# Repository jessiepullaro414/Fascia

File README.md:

# Fascia — KiCad schematic + PCB

Companion KiCad project for "Fascia", a 10-inch Android Automotive touch
display head unit: sibling to
[`manifold-pcb`](https://github.com/jessiepullaro414/Manifold),
[`thermo-pcb`](https://github.com/jessiepullaro414/Thermo) and `ecu-pcb`,
same 12V automotive constraints as the rest of the family.

Unlike the rest of the family this is a **two-board** project, because the
panel is physically detached from the main board and sits across the dash
from it:

1. **Carrier board** (behind the dash) — a Toradex Verdin iMX95 System on
   Module on a custom carrier: automotive 12V front end, LVDS display
   output via a DSI-to-LVDS bridge, backlight control, CAN FD to talk to
   `ecu-pcb`, line-level audio pre-outs to an external amplifier, a
   microphone input, and USB-C for wired CarPlay / Android Auto.
2. **Panel board** (in the bezel) — terminates the ribbon at the screen:
   panel LVDS connector, capacitive touch controller, backlight LED
   connector.

Bluetooth and Wi-Fi need no carrier hardware — they come with the
module's `WB` variant.

## Status

**PCB placed and routed to within 3 connections.**
`build_pcb.py` generates `Fascia.kicad_pcb`: 118 footprints, 574 pads
netted across 129 nets, six layers, on a **148 x 71 mm** board.
`route_board.py` (ported from the sibling boards) routes it with
FreeRouting, widens the power trunks, pours GND on In1 and In4, and then
asks `kicad-cli` DRC how many connections are really open. After a
150-pass run **3 connections are still unrouted**: `AOUT_RL_N` (codec to
the audio connector), `U9_ADR1_TIE`, and `LVDS_A_Y0N` (bridge to panel
connector). FreeRouting oscillated between 3 and 4 for the last 100
passes, so more passes of the same run will not close them; they need a
second stochastic attempt or hand-routing. `run_drc.py` reports
**schematic parity 0**, 12 `lib_footprint_mismatch` findings that are a
KiCad tooling artifact, and one silkscreen-over-mask finding.

Nothing about the differential pairs is tuned: FreeRouting does not
length-match, so the DSI and dual-link LVDS pairs are ordinary routed
nets with no impedance control. `route_board.py` prints the resulting
intra-pair skew so it is a number, not a guess.

Placement uses the **same skyline bottom-left packer as `manifold-pcb`
and `thermo-pcb`**, ported rather than reinvented, with three additions
this board needed:

- **Every part is tried both unrotated and rotated 90 degrees**, and goes
  wherever it yields the lowest resulting top edge. That is what turns
  the tall pin-header connectors on their sides and lets the 0603s
  backfill the low spots beside the big parts.
- **Keepouts are real packer inputs**, not checks applied afterwards.
- **The bridge, socket and panel connector are placed first** (`PIN_FIRST`
  in `build_pcb.py`), so the DSI-to-LVDS bridge sits beside the Verdin
  socket instead of 75 mm away. Area order alone had put it there, and
  nearly every open net in the first routing run was at that bridge.
- **A passive goes near its own IC** (`PULL`). Once its anchor IC is
  down, a passive takes the slot closest to it, with a height penalty so
  it cannot strand a void below. Plain lowest-gap order had put a
  pull-up 130 mm from the chip it belongs to. Estimated wirelength fell
  from 7,612 to 5,895 mm (`tools/placement_metric.py`), and FreeRouting
  at 12 passes went from 22 unrouted to 4.
- Spacing between parts (`CLEAR`) is 2.0 mm, up from 1.3. That alone took
  12-pass routing from 22 unrouted to 11, at a cost of 7 mm of height.

Group membership is derived from the netlist: each part joins whichever
IC or connector it shares the most **non-rail** nets with. Rails are
excluded deliberately: GND touches everything and would make every part
look equally related to everything else.

The Verdin socket is rotated 90 degrees as part of that. Its footprint is
36 x 79 mm, tall and narrow; on its side it is 79 x 36 mm and the board
becomes landscape, which is also the shape a dash opening wants.

**Schematic complete — every block wired except the backlight.**
`build_schematic.py` generates a real, KiCad-loadable schematic
containing the Verdin iMX95 X1 connector, the 12 V automotive front end,
the 5 V buck, the 1.8 V and 3.3 V rails, CAN FD, the SN65DSI85-Q1
DSI-to-LVDS bridge, the PCM3168A-Q1 audio subsystem with its level
shifters, the USB-C port, and the control/sequencing block. No PCB yet.

`kicad-cli sch erc` reports **10 violations**, and every one is either
blocked on a datasheet that has not arrived or deliberately optional:

| What | Count | Why it is still open |
| --- | --- | --- |
| `PWM_3_DSI`, `GPIO_10_DSI` | 2 | Backlight — needs the iFan string voltage and current |
| `USB_2_*` | 4 | Panel touch link — needs the panel's touch interface confirmed |
| `CAN_2_*` | 2 | Optional second CAN bus; no consumer chosen |
| `DSI_IRQ` | 1 | Bridge interrupt; wants a spare 1.8 V module GPIO |
| `IGN_SENSE` | 1 | Ignition sense; wants a module ADC input |

**160 pins carry real NoConnect items and 40 signal nets are wired.**

**Footprints are assigned and verified.** Every part maps to a real
footprint, and the build checks that each named file actually exists — a
mistyped library path is otherwise invisible until the netlist reaches
the PCB editor and silently drops the part.

### The LM61460-Q1 footprint is generated, not borrowed

TI's RJR0014A (VQFN-HR-14) has no KiCad library footprint, and it is not
something a generic QFN generator can produce: the pads are all different
sizes, unevenly spaced, and **the four corner pads are L-shaped**.

`tools/build_lm61460_footprint.py` builds it. The geometry is not
eyeballed off the drawing — the LAND PATTERN EXAMPLE on page 55 of TI
SNVSB70F is real vector art, so the pad rectangles were extracted from
the PDF's own path data and only the *scale* had to be inferred, from a
dimension the drawing states outright (pad 10 is 2.4 × 0.4 mm). That
scale then reproduced pad 10's 0.400 mm height exactly, which is what
makes the rest of the extraction trustworthy.

Each L-shaped pad is built from **two rectangles sharing one pad
number** — a real KiCad construction this project has met before, in a
Keystone fuse holder with two physical pads both numbered "1". It is far
safer than approximating an L with its bounding box, which would put
copper in the notch and eat the clearance to the neighbouring pads.

All four notches face the *outer* corner of the pattern, confirmed by
rendering the drawing around pads 1, 9 and 11 rather than assuming the
symmetry held.

The generator verifies itself twice: internally, that the pad table is
coherent (pin numbering, which pads are L-shaped, pad 10's dimensions,
overall extent, and that no two *different* pins overlap), and then by
**loading the result back through KiCad's own engine**. That second check
earned its place immediately — the first version emitted trailing
`; PINNAME` comments on the pad lines, and KiCad's s-expression format
has no comment syntax, so the whole library failed to load with nothing
more useful than "Unable to load library".

The Verdin module plugs into a standard DDR4 SODIMM socket, and KiCad's
`SODIMM-260_DDR4_H4.0-5.2_OrientationStd_Socket` has exactly 260 pads
numbered 1–260 — a direct match for the extracted pinout, so the biggest
footprint risk on this board turned out to be no risk at all.

### Exposed pads are three different decisions

Every one of these footprints numbers its exposed pad N+1 — 65 on the
TQFP-64s, 25 on the VQFN-24, 9 on the SON-8s. Each symbol therefore
carries an explicit `EP` pin, so what happens to that pad is a visible
decision on the schematic rather than an accident of the pad having no
net:

| Part | Exposed pad |
| --- | --- |
| **LM74930-Q1** | **NoConnect — must float.** The datasheet forbids grounding it |
| TLV767-Q1, TPS2557-Q1 | GND |
| SN65DSI85-Q1, PCM3168A-Q1 | GND (PowerPAD is reference ground) |

The LM74930-Q1's NoConnect is load-bearing: without an explicit pin,
that pad is merely netless, and nothing on the drawing would stop a
later ground-stitching pass from claiming it.

What is already final:

- all 260 X1 pins exist, banked into 6 units
- 47 GND pins tied to ground, 5 VCC pins tied to +5V
- 158 unused pins carrying real `NoConnect` items
- **LM74930-Q1 front end fully wired** — back-to-back FETs with `A` and
  `OUT` on the shared source node, sense resistor with its 50 Ω tap into
  `CS+`, `OVCLAMP` tied to `OV` for clamp-with-breaker rather than plain
  disconnect, and the OV/UVLO dividers, timer, ILIM and IMON networks
- **LM61460-Q1 5 V buck fully wired** — `BIAS` to the output rail (valid
  because Vout ≤ 12 V), boot network through `RBOOT`, FB and EN dividers,
  `RT`, and pull-ups on the open-drain `FLT` and `PGOOD` outputs
- **TLV767-Q1 1.8 V LDO wired** — an LDO rather than a buck on purpose:
  small load, and no switching noise added to a board carrying LVDS next
  to a car radio. This rail exists because the module's I/O is 1.8 V
  logic; it feeds the CAN transceiver's VIO now and the bridge later
- **TCAN1044V-Q1 CAN FD link wired** — split termination (2×60 Ω with a
  midpoint capacitor to ground, which shunts common-mode noise on a bus
  leaving the enclosure on a harness), separate 5 V VCC and 1.8 V VIO
  decoupling, and a pull-down on `STB` because the part's internal
  pull-up would otherwise wake it in standby
- the module's `CAN_1_TX` / `CAN_1_RX` now reach the transceiver
- **SN65DSI85-Q1 bridge wired** — DSI channel A in, both LVDS links out,
  all twelve VCC pins on 1.8 V, `VCORE` treated as the 1.1 V *output* it
  is with its 1 µF, `REFCLK` resistor-pulled to ground since the pixel
  clock comes from the D-PHY clock, `ADDR` strapped low, and the unused
  DSI channel B inputs plus both RSVD pins left genuinely unconnected
  with NoConnect items rather than tied off
- `J4` panel LVDS connector, **provisional** — carries all 20 LVDS
  signals, but its real pin order and pin count await the panel datasheet
- **PCM3168A-Q1 audio codec wired** — five differential pre-outs (front
  L/R, rear L/R, sub) to `J5`, microphone into the first differential ADC
  input, TDM on `DIN1`, `MODE` strapped low for the I2C control port
- **A 3.3 V rail and two SN74AXC4T245-Q1 level shifters**, because the
  codec's digital domain cannot be wired directly to the module — see
  "The audio block needs level shifters" below
- **I2C crosses domains through the classic two-FET translator** rather
  than a push-pull part, which cannot pass an open-drain bus
- **USB-C port wired** — TPS2557-Q1 switching VBUS with a ~3.3 A limit,
  Rp resistors on both CC pins advertising 3 A from a downstream-facing
  port, ID strapped low for host mode, a divided VBUS sense back to the
  module, and ESD on every pin a passenger can touch. No PD controller
  and no negotiation firmware.
- **Control and sequencing wired** — JTAG header, power/recovery/reset
  buttons, and the RTC coin cell behind the ≥47 kΩ current-limiting
  resistor the datasheet requires (a lower value can stop the module
  booting). `CTRL_PWR_EN_MOCI` now gates the 1.8 V and 3.3 V LDOs, so
  the carrier rails follow the module instead of racing it at power-on.
- every pin on all nine ICs either netted or explicitly NoConnected

### The generator checks for silently merged nets

Blocks are laid out independently, so two can drift into the same region
and land one net's stub endpoint exactly on another's. That **merges the
two nets** — electrically catastrophic and near-invisible on the drawing.
It happened twice while building this schematic:

1. a codec decoupling cap's ground stub landed on the power tree's
   `UVLO_DIV` label;
2. the USB block's `USB_ILIM` stub landed on connector unit D's
   `USB1_VBUS_SENSE` stub.

ERC does report this as `multiple_net_names`, but only for the pair it
happens to notice and only after the fact. `build_schematic.py` now
records every terminated coordinate — pin positions *and* stub
endpoints, for both generic parts and the X1 connector — and fails
loudly, naming both nets and both owning references. The first version
of that check scanned only label positions and missed the second case
entirely, which is why it now tracks points rather than labels.

### The audio block needs level shifters (and why that is not optional)

The PCM3168A-Q1 has two supply domains: analog VCC at 4.5–5.5 V and
**digital VDD at 3.0–3.6 V**. VDD cannot be run at 1.8 V, so the codec
cannot share the module's logic level. Reading the electrical table
makes the consequence sharper than "it needs a translator":

| | Codec | Verdin |
| --- | --- | --- |
| Input high, min | **2.0 V** | drives 1.8 V max |
| Output high, min | **2.4 V** | **2.1 V absolute maximum** |

The first row means the module cannot reliably drive the codec. The
second row is the dangerous one: the codec's output high is *above the
module's absolute maximum rating*. Wired directly, the codec-to-module
direction would not merely fail — it would damage the module.

So every digital line between them is translated: I2S and the clocks
through SN74AXC4T245-Q1 translators, and I2C through the classic
two-N-FET open-drain circuit, because a push-pull translator cannot pass
a bus where either end may pull low.

What exists right now:

- `tools/extract_verdin_pinout.py` — extracts the full 260-pin Verdin
  iMX95 X1 connector pinout from Toradex's own hardware datasheet.
- `verdin_pinout.py` — the generated result: all 260 pins, 47 GND, 5 VCC,
  and the 20 LVDS pins, cross-checked against a second independent table
  in the same document.
- `verdin_x1.py` — functional banking of those 260 pins into multi-unit
  symbol units, with a verifier that proves the banking is a true
  partition of the connector.
- `build_schematic.py` — generates `Fascia.kicad_sch`, `Fascia.kicad_sym`,
  `sym-lib-table` and (on first run only) `Fascia.kicad_pro`.

Three things that were needed to get the first ERC pass down from 268
findings to the real ones, recorded because each cost a debug cycle:

1. **Power symbols must touch the net graphically.** A power symbol's own
   pin sits at its local origin with zero length, so placing it *near* a
   connector pin leaves both dangling — 155 `pin_not_connected` findings.
   The fix is a short stub wire from the pin out to the symbol, which
   also keeps the symbol graphic off the pin name.
2. **PWR_FLAGs need the same graphical reachability.** A flag placed in
   isolation, relying on name-based net merging, does not satisfy
   `power_pin_not_driven` (54 findings). Placing each flag on a real
   point of its net clears it.
3. **`kicad-cli` needs a `.kicad_pro` to resolve `${KIPRJMOD}`.** Without
   one it cannot find the project-local `sym-lib-table` and reports one
   `lib_symbol_issues` warning per placed symbol (60 findings), even
   though the symbols are embedded in the schematic and perfectly valid.

Everything below the "Design decisions" section is a plan, not a
description of something that exists. See "Known open items".

### Why X1 is banked into units

A 260-pin connector cannot be one schematic symbol — at 2.54 mm pitch a
single block is ~330 mm tall, taller than any sheet this project uses.
KiCad's answer is a multi-unit symbol, so `verdin_x1.py` assigns each pin
to a unit based on how *this board* uses the connector:

| Unit | Pins | Contents |
| --- | --- | --- |
| A | 55 | Power and ground |
| B | 16 | Control, sequencing, JTAG, tamper |
| C | 15 | Display — the DSI link to the bridge, plus backlight control |
| D | 16 | Communications — CAN to `ecu-pcb`, I2C, USB 2.0 for touch |
| E | 158 | Unused on this board (gets NoConnect items) |

Banks are derived from pin *names* rather than hand-listed pin numbers,
so re-running the extractor against a newer datasheet revision cannot
silently desynchronise the two files. That only works if the rules stay
exhaustive, which `verify()` enforces: every pin exactly once, nothing
invented, nothing dropped, plus explicit assertions on the two groupings
most worth getting right —

- the **display bank** must be exactly the 15 pins from datasheet
  Table 22, asserted by number rather than trusted to a pattern;
- the **USB split** must put the USB 2.0 data pair in the comms bank and
  SuperSpeed in the unused bank. This board's only USB is a 2.0 host port
  for the panel's touch controller, so the SS pairs are unused *on
  purpose*. Worth an explicit rule because they appear under two
  different naming styles — Verdin-standard `USB_2_SS*` and
  module-specific `USB1_TX1_*`/`USB1_RX1_*` — and a single `USB_` pattern
  silently catches one and misses the other.

Bank E is not filler. Per this project's KiCad notes a deliberately
unused pin needs a real `NoConnect` item, not a stub label, or ERC
reports it as a dangling/isolated label — so the unused pins have to be
enumerated as carefully as the used ones.

## Why this SoC, and why not the one I started with

The project began as "10-inch Android Automotive display on an NXP
i.MX 93". **The i.MX 93 cannot run Android**, and this was worth catching
before any board work started:

- The i.MX 93 has no 3D GPU — only the PXP 2D pixel pipeline.
- Since Android 10, NXP has excluded GPU-less i.MX parts from Android
  support outright, because Android's GPU and extension requirements
  can't be met. Running it would mean maintaining a private Android fork
  on software rendering.
- NXP's current i.MX Android BSP covers the 8M Mini/Nano/Plus/Quad, 8ULP,
  8QuadMax/XPlus and i.MX 95. Not the 93.

Replaced with the **i.MX 95**, which has an Arm Mali-G310 (OpenGL ES 3.2,
Vulkan 1.2, 2D+3D), is on NXP's Android BSP list, and is automotive
qualified.

### Why a SoM instead of a raw i.MX 95

A raw i.MX 95 is a 19×19 mm BGA paired with LPDDR5. That forces HDI
construction (laser microvias, blind/buried vias, 12–14 layers just to
escape the BGA) and roughly 90 length- and skew-matched LPDDR5 nets.

That last part is the disqualifier for this project specifically:
FreeRouting cannot do length-matched differential DDR routing, so the DDR
work would have to be manual — which directly contradicts this family's
rule that the generator scripts are the source of truth and the board is
always regenerated, never hand-edited.

Putting the SoC on a **Toradex Verdin iMX95** module moves the LPDDR5 and
its HDI stackup onto a part Toradex has already qualified, and leaves a
carrier board that is connectors, power and differential pairs — squarely
inside what the existing generate → route → verify pipeline handles.

## Design decisions

### Display link: 1920×1200, DSI-to-LVDS bridge on the carrier

The panel is detached and 20 cm–1 m away across the dash, so the link
that crosses that gap must be **LVDS** — differential and low-swing, so
it survives alternator and ignition noise. Options for the long run:

| Option | Verdict |
| --- | --- |
| **LVDS over shielded FFC** | **Chosen for the cable run.** Robust over a dash-length ribbon, and what 10.1" panels natively accept. |
| MIPI DSI direct to the panel | Rejected. D-PHY is designed for on-PCB or very short flex (~15–20 cm); unshielded ribbon across a dash is an EMI problem. |
| HDMI | Not native on the module. Needs a DSI-to-HDMI bridge on the carrier *and* a receiver board behind the panel bridging back. Two extra bridges. |
| FPD-Link III / GMSL2 | The right answer for genuinely long runs (10 m+), overkill and expensive here. |

**How the LVDS gets generated is the part that took real work.**

The module's own display ceilings, from datasheet Table 3: **LVDS 1× up
to 1920×1080**, **MIPI DSI 1× quad lane up to 4K**.

The 10.1" panel market is overwhelmingly **16:10** (1280×800 and
1920×1200), not 16:9. 1920×1200 needs ~154 MHz of pixel clock, which is
**above the module's 1920×1080 native LVDS ceiling** — both Toradex and
NXP's summary cap i.MX 95 LVDS at 1080p60. Forum figures of 170 MHz for
dual-channel split mode are **i.MX 6**, a different generation, and must
not be extrapolated to this part.

So: take **MIPI DSI off the module** (where 1920×1200 is far inside the
4K ceiling) and convert to dual-channel LVDS **on the carrier board**,
right at the ribbon connector, with a **TI SN65DSI85-Q1** — AEC-Q100
qualified, dual-channel LVDS out, 24 bpp, pixel clock 25–154 MHz.

The DSI run stays on-PCB where D-PHY is happy (centimetres); the long,
noisy dash run is still LVDS. Cost is one bridge IC.

**The module's native LVDS pins (88–144) are therefore unused.** They
remain documented in `verdin_pinout.py` in case the design ever falls
back to 1080p native.

**Unexpected benefit:** the whole DSI pin group sits on Verdin-standard
*Reserved* pins (17–55) rather than the *Module-specific* pins native
LVDS uses. This design is therefore **more** portable to other Verdin
modules than the native-LVDS version would have been — it inverts the
portability caveat noted below.

**Confirmed DSI pin group** (Verdin iMX95 datasheet Table 22), which
carries not just the lanes but every control signal the bridge and
backlight need:

| X1 pin | Signal | Role |
| --- | --- | --- |
| 23 / 25 | DSI_1_D3_N / _P | DSI data lane 3 |
| 29 / 31 | DSI_1_D2_N / _P | DSI data lane 2 |
| 35 / 37 | DSI_1_CLK_N / _P | DSI clock |
| 41 / 43 | DSI_1_D1_N / _P | DSI data lane 1 |
| 47 / 49 | DSI_1_D0_N / _P | DSI data lane 0 |
| 53 / 55 | I2C_2_DSI_SDA / SCL | SN65DSI85-Q1 configuration |
| 17 | GPIO_9_DSI | bridge enable |
| 19 | PWM_3_DSI | backlight brightness |
| 21 | GPIO_10_DSI | backlight enable |

### SN65DSI85-Q1: confirmed from the TI datasheet (SLLSEJ4B)

The mode this whole design depends on is **explicitly supported** —
datasheet Table 5, "Single DSI Input to Dual-Link LVDS":

> Single DSI Input on Channel A to Dual-Link LVDS output with Odd pixels
> on Channel A and Even pixels on Channel B.

Register configuration for that mode:

| CSR | Field | Value |
| --- | --- | --- |
| 0x10.6:5 | `DSI_CHANNEL_MODE` | `01` — single-channel DSI receiver |
| 0x10.4:3 | `CHA_DSI_LANES` | `00` — four lanes enabled |
| 0x18.4 | `LVDS_LINK_CFG` | `0` — dual-link LVDS |
| 0x18.3 | `CHA_24BPP_MODE` | `1` — 24 bpp |
| 0x18.1 / 0x18.0 | `CHA/CHB_24BPP_FORMAT1` | selects Format 1 vs Format 2 |

Other confirmed facts that drive the schematic:

- **AEC-Q100 Grade 2, −40 °C to +105 °C ambient.** Better rated than the
  Verdin module itself, and consistent with the rest of this family.
- **Single 1.8 V supply** (VCC 1.65 / 1.8 / 1.95 V). No second rail.
- **HTQFP-64 (PAP)** with thermal pad. RθJA 36.1 °C/W, max case
  temperature 92.2 °C — the pad needs a real thermal via field.
- **REFCLK (pin 17) is optional** — the LVDS pixel clock can be sourced
  from the free-running D-PHY clock instead. If unused it **must be
  pulled to ground through an external resistor**, not left floating.
- **ADDR (pin 64)** selects the I2C target address; if strapped high it
  must go to the *same* 1.8 V rail as VCC, not any other 1.8 V source.
- **IRQ (pin 33)** is an interrupt output back to the SoC.
- **EN** may be driven by `GPIO_9_DSI` or by an RC (≈200 kΩ + ≈200 nF).
  It must only go high *after* VCC is valid. To reset with VCC already
  high, EN must be held low ≥10 ms.
- **Sequencing constraint for the driver:** the DSI CLK lane must be in
  HS and the DSI data lanes driven to LP11 while the device is in reset,
  before EN is asserted.
- For 18 bpp the `Y3` pairs are left NC; at 24 bpp all four data pairs
  per link are used — so the panel connector carries 10 pairs.
- `CHA_SYNC_DELAY` must be programmed to at least 32 pixel clocks.

**Everything is configured over I2C — there is no format strapping.**
That is a meaningful de-risking result: the VESA-versus-JEIDA mapping
question is a *software* choice (`24BPP_FORMAT1`), so picking the panel
later cannot force a board respin over it.

### Timing margins — corrected

An earlier revision of this file claimed 1920×1200 sat "exactly at the
bridge's 154 MHz ceiling". **That was wrong**, and the error mattered:
the 25–154 MHz figure is the **LVDS output clock per link**, and in
dual-link mode each link carries half the pixels. TI's own power-table
reference case is literally 1920×1200 dual-link with
**LVDS CLK OUT = 81.6 MHz**.

The real picture, with every number now confirmed against a primary
source:

| Constraint | Value | Limit | Utilisation |
| --- | --- | --- | --- |
| i.MX 95 DSI transmit, per lane | ~925 Mbps | **2500 Mbps** | **~37% — huge headroom** |
| LVDS output clock, per link | ~81.6 MHz | 154 MHz | ~53% — comfortable |
| **Bridge DSI input, per lane** | ~925 Mbps | **1 Gbps** | **~93% — the bottleneck** |

The i.MX 95 side is confirmed a non-issue: **IMX95AEC Rev 8, Table 58,
`RATE[TX]` Transmit Serial Data Rate = 80 to 2500 Mbps per lane**, and
the feature summary lists "1x 350 MHz MIPI-DSI (4-lane, 2.5 Gbps/lane)
supporting 4kp30 or 3840 x 1440p60".

So the **SN65DSI85-Q1 is the sole bottleneck** in the chain. That is
acceptable — TI documents 1920×1200 as a supported use case for this
part — but it means the bridge, not the SoC, is what to re-examine if
the timing ever fails to close.

The same datasheet confirms the native LVDS ceiling recorded above:
"2x 1080p60 LVDS Tx (2x 4-lane or 1x 8-lane)".

- 1920×1200p60 CVT-RB ≈ 154 MHz pixel clock × 24 bpp = ~3.70 Gbps across
  4 lanes = ~925 Mbps/lane. Under the bridge's 1 Gbps limit, with ~7%
  headroom.
- With **standard** (non-reduced) blanking the pixel clock is ~193 MHz →
  ~1.16 Gbps/lane, which **exceeds** the bridge limit (though not the
  SoC's). Reduced-blanking timing is therefore mandatory, not merely
  preferable.
- Fallback remains 1920×1080, which relaxes the DSI side to
  ~830 Mbps/lane.

### Layout constraints (i.MX 95 Hardware Design Guide UG10210 Rev 2.0)

- **100 Ω differential** for MIPI DSI *and* LVDS, ±10% (Table 40). Also
  50 Ω single-ended for everything else unless specified. This sits
  comfortably inside the SN65DSI85-Q1's own 90–132 Ω LVDS output range.
- For MIPI-DSI compliance tests 1.1.4/1.1.5, keep **parasitic
  capacitance of each DSI trace below 10 pF** — relevant because the DSI
  run crosses the carrier from X1 to the bridge.
- The module's unused native LVDS pins are simply left **not connected**
  (datasheet Table 4). The `VDD_LVDS_1P8`-to-ground-via-10 kΩ guidance in
  that same table applies to the SoC, which is Toradex's side of the
  boundary, not this carrier's.

Note the Verdin carrier must still follow Toradex's own Carrier Board
Design Guide (doc 108140) for anything X1-side; UG10210 describes the
raw SoC.

For reference, the module's native LVDS pins, should the fallback be
needed:

| X1 pin | Channel 0 | X1 pin | Channel 1 |
| --- | --- | --- | --- |
| 88 / 90 | LVDS0_CLK_N / _P | 118 / 120 | LVDS1_CLK_N / _P |
| 94 / 96 | LVDS0_D0_N / _P | 124 / 126 | LVDS1_D0_N / _P |
| 100 / 102 | LVDS0_D1_N / _P | 130 / 132 | LVDS1_D1_N / _P |
| 106 / 108 | LVDS0_D2_N / _P | 136 / 138 | LVDS1_D2_N / _P |
| 112 / 114 | LVDS0_D3_N / _P | 142 / 144 | LVDS1_D3_N / _P |

### Candidate panels evaluated

Real parts found, with the specs that actually drive the board design:

**Selected: iFan IF101GRL192-120B** (2026-08-16), pending the vendor
datasheet and pricing. Chosen mainly on temperature — it is a full 10 °C
better at both ends than the other 1920×1200 candidate, which is the
difference between reliable and marginal on a sun-baked dash — with 89%
DCI-P3 gamut as a real bonus for image quality.

<https://ifan-display.com/product/10-1-inch-touch-panel-1000-nits-wide-color-gamut-1920x1200/>

| Part | Res | Nits | Interface | Touch | Bonded | Temp |
| --- | --- | --- | --- | --- | --- | --- |
| **iFan IF101GRL192-120B** ← selected | 1920×1200 | 1000 | LVDS, 60-pin | **PCAP inc.** | ? | **−30 to +80 °C** |
| Riverdi RVT101HVLNWC00-B | 1280×800 | ~1000 | LVDS | PCAP inc. | **yes** | industrial |
| CDTech S101BWU78EP | 1920×1200 | 1000 | LVDS, 45-pin FPC | no | no | −20 to +70 °C |
| CDTech S101HWX101ED | 1280×800 | 1000 | 4-lane LVDS, 40-pin FPC | no | no | −30 to +80 °C |
| CDTech S101HWX80NP-FC81 | 1280×800 | 350 | 1-ch LVDS, 30-pin | ILI2511 (USB) | no (G+G) | −20 to +70 °C |
| AUO G101UAN02.0 | 1920×1200 | 800 | **MIPI** | no | no | **−10 to +60 °C** |

**The market bifurcates, and neither half is the full target spec:**

- You can get **1920×1200 + 1000 nit + touch** (iFan), but optical
  bonding is unconfirmed and there is no public datasheet — it is a
  contact-the-vendor part.
- Or you can get **productized optical bonding + PCAP + real datasheets
  + distributor stock** (Riverdi), but only at 1280×800.

The full combination is realistically a **semi-custom order with MOQ**,
not an off-the-shelf purchase.

AUO's G101UAN02.0 is ruled out on two counts despite being the obvious
1920×1200 name: it is **MIPI, not LVDS** (which would put D-PHY on the
dash ribbon, the thing this whole design avoids), and −10 to +60 °C is
unusable in a car.

Three things to carry forward:

1. **The backlight boost designs are not interchangeable** — 27–34 V at
   240 mA versus 13.5–17 V at 360 mA versus 5 V at 530 mA are three
   different converters. The panel must be chosen before the backlight
   circuit is designed. iFan publishes only a total figure (9.32 W), so
   the string configuration has to be asked for.
2. **Temperature does not track resolution.** CDTech's 1920×1200 part is
   −20 to +70 °C while their 1280×800 is −30 to +80 °C. A dash bakes in
   sun, so this is a real selection criterion, not a footnote — it is the
   main reason the iFan part leads.
3. **Touch is often USB, not I2C.** Both CDTech modules with touch use
   USB controllers (ILI2511), and iFan lists "USB/I2C". This matters —
   see below.

### Touch interface: USB may beat I2C over this cable run

The original plan assumed I2C touch. The market says otherwise, and on
reflection USB is probably the better engineering choice here anyway:

- **I2C is single-ended** and was designed for on-board use. Over 20 cm
  it is fine; over a metre it is marginal — bus capacitance eats the
  rise time and there is no noise rejection in a car's environment.
- **USB is differential and designed for cables.** A metre is nothing.
  It also arrives as a standard HID device, so Android needs no custom
  touch driver or device-tree work.
- Cost is one differential pair on the ribbon instead of two
  single-ended wires, and a USB host port on the carrier — which the
  Verdin already has.

Decision still open, but it should be made on cable length, not on
which is simpler on paper.

### Power tree and part selection

Every part below was verified against its own datasheet, not chosen from
memory. Two of them corrected an earlier wrong guess, noted inline.

| Role | Part | Key evidence |
| --- | --- | --- |
| Front-end protection | **LM74930-Q1** | AEC-Q100 grade 1 (−40/+125 °C), 4–65 V in, reverse protection to −65 V, adjustable OC/OV, circuit breaker, "meets automotive ISO7637 transient requirements with a suitable TVS diode" |
| 12 V → 5 V buck | **LM61460-Q1** | AEC-Q100 grade 1, 3–36 V in (42 V transient), 6 A, synchronous, low-EMI with spread spectrum |
| CAN FD | **TCAN1044V-Q1** | AEC-Q100 grade 1, VIO 1.7–5.5 V with explicit 1.8 V support, CAN FD to 8 Mbps, ±58 V bus fault protection |
| DSI→LVDS bridge | **SN65DSI85-Q1** | AEC-Q100 grade 2 (−40/+105 °C), single 1.8 V rail, HTQFP-64 |
| Audio codec | **PCM3168A-Q1** | AEC-Q100, 24-bit 6-in/8-out codec, differential outputs, I2S/TDM, 104 dB, 64-HTQFP |
| USB VBUS switch | **TPS2557-Q1** | Automotive, current limit adjustable 500 mA–5 A, FAULT output, dual thermal sensing |
| Wi-Fi / Bluetooth | **on-module** (u-blox MAYA-W260-00B) | Wi-Fi 6, Bluetooth Classic/LE 5.4, two U.FL connectors — comes with the Verdin `WB` variants |

**The module sets two hard constraints** that drove these choices:

- **VCC is 3.135–5.5 V**, so the main rail is 5.0 V.
- **Verdin I/O is 1.8 V logic** (absolute max 2.1 V). This is the
  constraint that eliminates most automotive CAN transceivers.

#### Front-end topology (resolved from the datasheet, not inferred)

TI's own front-page reference circuit for the LM74930-Q1 is titled
**"VBAT 12-V or 24-V With 200-V Unsuppressed Load Dump — Output Clamp"**.
That is this application almost exactly: an unsuppressed alternator on a
1972 car, with the output clamped rather than disconnected.

The back-to-back FET arrangement is easy to get backwards, so it is
written down here:

```
VBAT ──[RSENSE]──┬── Q2 drain            Q2 = pass / load switch  (HGATE)
                 │                       Q1 = ideal diode         (DGATE)
                 Q2 source ──┬── COMMON ──┬── Q1 source
                             │            │
                        OUT (15)      A (2)      ← both pins on COMMON
                                                    (common-source pair)
                                       Q1 drain ── VOUT_PROT ── C (24)
```

The resolution: **`A` (2) and `OUT` (15) are the same node.** "Back-to-back
N-channel MOSFETs in common source configuration" means both FET sources
tie together, and the datasheet independently says `A` is "the source of
the external ideal diode MOSFET" while `OUT` is "the common source rail".
`C` (24) is the ideal diode's drain and therefore the protected output.
Direction is confirmed by the ideal-diode spec regulating "10.5 mV **A to
C** forward voltage drop", and by `HGATE` driving "the **first** MOSFET in
the power path".

Reference-design support components, all named in that circuit: `RSENSE`
with `RSET` (50 Ω into `CS+`), `RISCP` on `ISCP`, `RILIM` on `ILIM`,
`RMON` on `IMON`, `CT` on `TMR`, `CVS` on `VS`, `CCAP` across `CAP`–`VS`,
and the `R1`/`R2`/`R3` dividers feeding `OV`/`OVCLAMP` and `UVLO`.

#### The 5 V rail needs splitting

Rough budget, with the module figure still a placeholder:

| Load | Estimate |
| --- | --- |
| Verdin iMX95 | ~3 A @ 5 V (unknown — see open items) |
| USB-C charging | 3 A @ 5 V |
| Bridge, codec, CAN, misc | ~0.5 A |
| **Total on 5 V** | **~6.5 A** |

That is over the LM61460-Q1's 6 A, so **two supplies** rather than one
bigger one: a main rail for the module and peripherals, and a second
dedicated to USB VBUS. Splitting is the better design anyway — a phone
drawing a fault current should not be able to brown out the SoC and
reboot Android. Using the same part twice also keeps the BOM narrow.

The backlight boost is deliberately *not* on the 5 V rail — it runs from
the protected 12 V directly, since the panel wants ~27–34 V and routing
that through 5 V would waste a conversion and eat the budget.

#### Bluetooth comes free with the module

The Verdin `WB` variants carry a u-blox **MAYA-W260-00B**: Wi-Fi 6,
**Bluetooth Classic / LE 5.4**, IEEE 802.15.4, and **two U.FL antenna
connectors already on the SoM**. That means no RF design, no antenna
matching and no radio certification work on this carrier — just two U.FL
cables out to external antennas.

Bluetooth Classic covers A2DP for streaming and HFP for hands-free calls.
Wi-Fi plus Bluetooth together is also exactly what **wireless CarPlay and
Android Auto** need, so the USB-C port is for wired mode and charging
rather than being the only way in.

Cost to record: the datasheet carries separate pin tables for "modules
without Wi-Fi", so the `WB` variant consumes some UART and ADC pins that
would otherwise reach the carrier. The variant has to be locked before
the connector banks are final.

#### Two corrections worth recording

**The CAN transceiver must be the `V` variant.** An earlier draft of this
plan named the TCAN1043-Q1, which only level-shifts to 3.3 V or 5 V — it
cannot talk to 1.8 V logic at all. Worse, within the correct family the
datasheet's own device comparison table reads:

| Part | Low-voltage I/O support on pin 5 |
| --- | --- |
| TCAN1044-Q1 | No — pin 5 is a No-Connect |
| **TCAN1044V-Q1** | Yes — pin 5 is VIO, 1.8–5.5 V |

The suffix is the entire difference. Order the wrong one and the board
assembles perfectly and the CAN link never works.

**The surge stopper is TI's, not the obvious ADI part.** The LTC4364 is
the better-known automotive surge stopper and does something the
LM74930-Q1 does not — it *regulates through* an overvoltage event rather
than disconnecting. But its datasheet order table lists only C, I and H
temperature grades with **no AEC-Q100 qualification**, which fails this
family's standard (see `ecu-pcb`, where the last unqualified part was
deliberately swapped out). The LM74930-Q1 is explicitly `-Q1`.

**Correction — the LM74930-Q1 does clamp through.** An earlier revision
of this file claimed it protects only by disconnecting the load, and
warned that a load dump would therefore collapse the 5 V rail and force
an Android reboot. That was wrong, and reading the pin table and spec
table settled it:

- pin 16 is **`OVCLAMP`**: "connect this pin to OV pin for overvoltage
  clamp with circuit breaker (timer) functionality";
- `OVCLAMP` has its own rising/falling thresholds (0.59 V / 0.45 V),
  separate from the plain `OV` disconnect thresholds;
- the timer spec includes **`I(TMR_SRC_OVCLAMP)`, "TMR source current
  during overvoltage clamp"** — a dedicated clamp state, not a
  disconnect;
- and `N(A_R_Count)` gives **32 auto-retry cycles**.

So it regulates the pass FET through an overvoltage event for a period
set by the TMR capacitor, then opens the breaker if the event outlasts
it, then auto-retries. That is genuine surge-stopper behaviour, and it
removes the reboot risk previously recorded here.

What remains real is that the clamp is **timed, not indefinite**: the TMR
capacitor has to be sized to ride out a 200 ms load dump, and the pass
FET has to survive dissipating it for that long. FET SOA selection is
therefore a genuine design task — see "Known open items".

For scale, the LTC4364 datasheet gives the industry-standard transient
shapes: a general automotive transient of tr = 10 µs / VPK = 80 V /
τ = 1 ms, and **load dump of tr = 5 ms / VPK = 60 V / τ = 200 ms**. The
200 ms one carries the energy that matters.

### Panel quality matters more than resolution here

Recorded because it should drive the panel budget. In a car, in rough
order of impact on how good the display actually looks:

1. **Brightness** — consumer panels (250–400 nits) wash out in direct
   sun; automotive panels run 800–1500 nits. This is the dominant factor
   and it drives the backlight boost design (string current, thermals).
2. **Optical bonding** (OCA/LOCA) — removes the air gap between LCD and
   cover glass that otherwise destroys daylight contrast; also prevents
   condensation.
3. **24-bit colour, not 18-bit** — 6-bit-per-channel LVDS panels band
   visibly on the dark gradients Android Automotive uses.
4. **IPS** — driver and passenger both view well off-axis.
5. **Anti-glare / AR coating.**

Resolution ranks below all of these. The target spec is a 1080p,
~1000-nit, optically-bonded, 24-bit IPS panel.

**Caveat worth recording:** LVDS on Verdin is a *Module-specific*
function, not an Always-Compatible or Reserved one (datasheet Table 6
classifies it `Total 1 / Always Compatible 0 / Reserved 0 /
Module-specific 1`). The pins are genuinely on the connector, but this
carrier is therefore tied to the Verdin iMX95 specifically and is not
portable to an arbitrary other Verdin module. MIPI DSI, by contrast, sits
on Verdin-standard Reserved pins (17–55) and would be portable — at the
cost of needing a bridge for a dash-length run.

This is also why `tools/extract_verdin_pinout.py` exists rather than a
hand-typed table: the LVDS pins are named `MSP_1`…`MSP_25` in the Verdin
specification column and only resolve to `LVDS0_CLK_N` etc. in the
module-specific function column. A parse that reads the wrong column
concludes the module has no LVDS at all.

### Other confirmed module facts

- Module: 69.6 × 35.0 × 6.0 mm, 260-pin DDR4 SODIMM edge connector.
- Odd pins top side, even pins bottom (DDR4 SODIMM numbering).
- 5 VCC pins (251, 253, 255, 257, 259), 47 GND, plus `VCC_BACKUP` (249).
- CAN FD: `CAN_1_TX`/`CAN_1_RX` on pins 20/22, `CAN_2` on 24/26.
- I2C_1 on pins 12/14; a dedicated display-side `I2C_2_DSI` on 53/55.
- Backlight: `PWM_3_DSI` (pin 19) for brightness, `GPIO_10_DSI` (pin 21)
  for backlight enable via the on-module PCAL6416A I/O expander.
- HDMI is explicitly *not* natively supported on this module.

## Planned scope

A head unit that **displays and sources audio but does not amplify it**.
Scope revised 2026-08-16 from the original display+touch+CAN.

In scope: display, touch, CAN to `ecu-pcb`, Bluetooth, line-level
pre-outs to an external amplifier, a microphone for calls and voice
control, and USB-C for wired CarPlay / Android Auto plus phone charging.

Explicitly **not** in scope: any power amplifier. This board drives no
speakers — it feeds an existing automotive amp over RCA-level pre-outs.
That single decision keeps the highest-current, highest-heat, highest-EMI
subsystem off the board entirely, which matters in a sealed dash
enclosure that already contains a 1000-nit backlight.

Also still out of scope: reversing camera, automotive Ethernet, and any
radio tuner.

Carrier board blocks:

- 12V automotive front end: reverse-polarity protection, load-dump
  clamping (ISO 7637-2 pulse 5), wide-Vin buck to the module rails.
- Verdin X1 260-pin SODIMM socket.
- Module power sequencing: `CTRL_PWR_EN_MOCI`, `CTRL_RESET_MOCI#`,
  `CTRL_SLEEP_MOCI#`, ignition/ACC sense.
- MIPI DSI from X1 into a **SN65DSI85-Q1** bridge — short, impedance-
  controlled, length-matched on-board runs; the bridge sits right at the
  panel connector so the DSI never reaches the ribbon.
- Bridge configured over `I2C_2_DSI`, enabled by `GPIO_9_DSI`.
- **Audio: PCM3168A-Q1 codec** on I2S/TDM from the module. Five of its
  eight DAC channels drive the pre-outs (front L/R, rear L/R, mono sub);
  one ADC channel takes the microphone. Differential outputs, which is
  the right choice for running line level across a car to an amp.
- **Microphone connector** for a remote mic mounted near the A-pillar or
  headliner, with bias. Placement beats mic quality in a car by a wide
  margin, which is why it is off-board.
- **USB-C port** for wired CarPlay / Android Auto: USB 2.0 data to the
  module's `USB_1` port, and VBUS from a **TPS2557-Q1** switch whose EN
  and FAULT map onto `USB_1_EN` and `USB_1_OC#`. CC1/CC2 carry Rp
  resistors advertising 3 A as a downstream-facing port — no PD
  controller and no negotiation firmware.
- Two **U.FL antenna** pigtails from the module's on-board wireless out
  to external Wi-Fi/Bluetooth antennas.
- Dual-channel LVDS out of the bridge to the panel connector, with
  common-mode chokes and ESD protection on each of the 10 pairs.
- Backlight boost driver, PWM-dimmed via `PWM_3_DSI`, enabled by
  `GPIO_10_DSI`, sized for a high-brightness (~1000 nit) panel rather
  than a consumer-grade one.
- CAN FD transceiver to `ecu-pcb`.

Panel board blocks:

- Ribbon connector from the carrier.
- Panel LVDS FFC connector — pin count set by the chosen panel (the
  leading candidate uses 60-pin).
- Capacitive touch controller — must live at the panel, since capacitive
  sensing will not tolerate a metre of cable between controller and
  sensor. Most candidate modules integrate it already. Interface back
  down the ribbon is **USB or I2C, still to be decided** (see "Touch
  interface" above).
- Backlight LED string connector.

## How it's built

Same script-driven, kiutils/kicad-cli-verified workflow as the sibling
projects: the generator scripts are the source of truth — always
regenerate from them, never hand-edit `Fascia.kicad_sch`/`Fascia.kicad_pcb`
directly.

`tools/extract_verdin_pinout.py` is a one-shot data extractor, not part of
the per-build pipeline. It takes the Toradex datasheet's local path as an
argument (the PDF is Toradex's document and is gitignored, not committed):

```bash
python tools/extract_verdin_pinout.py ~/Downloads/200007-verdin_imx95_datasheet.pdf
```

It refuses to write output unless all 260 pins parse and the LVDS pin
numbers it derived from the main pin-assignment tables agree with the
separate LVDS table on page 42.

## Known open items

- No BOM or fab outputs yet. See [PLAN.md](PLAN.md) for the full list of
  what is left and what each step is blocked on.
- **Panel selected but its datasheet is not yet in hand.** The
  **iFan IF101GRL192-120B** is chosen; a request for datasheet and
  pricing went to the vendor on 2026-08-16. Until it arrives, anything
  that depends on the panel's real numbers is blocked:
  - the backlight boost converter (no string V/I published)
  - the panel-side connector footprint and pinout (60-pin, mapping
    unknown)
  - the touch link (USB vs I2C, see above)
  - bezel/mechanical
- **Questions to put to iFan** — none are answerable from their public
  page:
  - Is optical bonding available, and at what MOQ?
  - LVDS single or dual channel? (1920×1200 at 24 bpp requires dual, so
    this is really a confirmation, but the 60-pin connector needs a
    pinout either way.)
  - Backlight string configuration — volts and milliamps, not just the
    published 9.32 W total. The boost converter cannot be designed
    without it.
  - Touch controller IC, and is the interface USB or I2C?
  - Connector part number, and is a mating FFC/cable available?
  - Operating temperature is quoted as −30 to +80 °C; confirm storage
    range and whether an automotive-qualified variant exists.
- **Touch interface undecided** — USB versus I2C, see the section above.
  Leaning USB on cable-length grounds.
- **DSI timing closes on paper but is not yet proven on hardware.** Every
  number in the chain is now confirmed against a primary source and
  1920×1200 fits, but with only ~7% headroom on the bridge's DSI input
  and a hard requirement for reduced-blanking timing. Worth confirming on
  a Verdin EVK with the real panel before committing to fab. Fallback is
  1920×1080.
- **LVDS mapping convention not yet fixed** — VESA vs JEIDA (a.k.a. SPWG)
  differ in bit ordering and are not interchangeable. Determined by the
  chosen panel.
- **Module temperature rating is industrial, not automotive.** The Verdin
  iMX95 IT variants are −40 °C to +85 °C, unlike the AEC-Q100 parts used
  across the rest of this family. Acceptable for a cabin/dash mount but a
  real deviation from the family's engine-bay-rated standard, and worth a
  deliberate decision rather than an accident.
- **Pass-FET SOA and TMR sizing.** The LM74930-Q1's overvoltage clamp is
  timed rather than indefinite, so the TMR capacitor must be sized to
  ride out a 60 V / 200 ms load dump, and the pass MOSFET must survive
  dissipating that event inside its safe operating area. Neither number
  is chosen yet, and SOA is the one most likely to drive the FET choice.
- **Watch the LM74930-Q1 thermal pad.** Its datasheet says the exposed
  pad (RTN) must be left **floating — explicitly "Do Not connect to GND
  plane"**. That is the opposite of the near-universal VQFN convention,
  so both the footprint and the PCB generator need a deliberate exception
  or the part will be destroyed by a routine ground stitch.
- **Verdin power consumption is still unknown.** The module datasheet
  gives no current figure, deferring to the Verdin Family Specification,
  which has not been pulled. The 5 V rail is provisionally sized on the
  LM61460-Q1's 6 A rather than on a real budget.
- **Unit E may need splitting.** At 158 pins it is ~200 mm per side,
  which fits an A3 sheet only marginally. Splitting it into two units of
  ~79 is the likely fix, but the real constraint will not be known until
  the symbol generator exists.
- Verdin iMX95 datasheet is marked *Preliminary — Subject to change*;
  the pinout should be re-extracted against a final revision before fab.
- Carrier must follow the Verdin Carrier Board Design Guide (Toradex doc
  108140), which has not yet been reviewed.
- Toradex publishes free reference carrier schematics with symbols and
  IPC-7351 footprints — not yet pulled in, but likely the right source for
  the X1 socket footprint rather than drawing one.

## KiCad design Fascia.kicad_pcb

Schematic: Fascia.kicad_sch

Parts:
C1: 100uF; C_0603_1608Metric
C2: 100n CVS; C_0603_1608Metric
C3: 100n CCAP; C_0603_1608Metric
C4: open CT; C_0603_1608Metric
C5, C9, C22: 10u in; C_0603_1608Metric
C6: 1u VCC; C_0603_1608Metric
C7: 100n boot; C_0603_1608Metric
C8: 44u out; C_0603_1608Metric
C10, C23: 10u out; C_0603_1608Metric
C11: 100n VCC; C_0603_1608Metric
C12: 100n VIO; C_0603_1608Metric
C13: 4n7 split; C_0603_1608Metric
C14: 1u VCORE; C_0603_1608Metric
C15: 10u 1V8; C_0603_1608Metric
C16, C17, C18, C19, C20, C21: 100n 1V8; C_0603_1608Metric
C24: 100n U7A; C_0603_1608Metric
C25: 100n U7B; C_0603_1608Metric
C26: 100n U8A; C_0603_1608Metric
C27: 100n U8B; C_0603_1608Metric
C28, C29, C30: 10u decouple; C_0603_1608Metric
C31, C32, C33, C34: 100n codec; C_0603_1608Metric
C35: 100n RST; C_0603_1608Metric
C36: 1u couple; C_0603_1608Metric
C37: 100n IN; C_0603_1608Metric
C38: 150u VBUS; C_0603_1608Metric
C39: 100n; C_0603_1608Metric
D1: TVS 33V; D_SMB
D2: ESD DP; D_SMB
D3: ESD DN; D_SMB
D4: ESD VBUS; D_SMB
F1: 5A; Fuse_Bourns_MF-RG300
J1: Verdin iMX95; SODIMM-260_DDR4_H4.0-5.2_OrientationStd_Socket
J2: Power in; PinHeader_1x03_P2.54mm_Vertical
J3: CAN to ECU; PinHeader_1x03_P2.54mm_Vertical
J4: Panel LVDS (provisional); PinHeader_1x22_P2.54mm_Vertical
J5: Pre-outs to amp; PinHeader_1x11_P2.54mm_Vertical
J6: Mic; PinHeader_1x03_P2.54mm_Vertical
J7: USB-C CarPlay; PinHeader_1x09_P2.54mm_Vertical
J8: JTAG debug; PinHeader_1x08_P2.54mm_Vertical
J9: Buttons; PinHeader_1x04_P2.54mm_Vertical
J10: RTC coin cell; BatteryHolder_Keystone_1058_1x2032
L1: 2.2u; L_1210_3225Metric
Q1: NFET diode; SOT-23
Q2: NFET pass; SOT-23
Q3, Q4: NFET i2c xlat; SOT-23
R1: 2m sense; R_0603_1608Metric
R2: 50R; R_0603_1608Metric
R3: RILIM; R_0603_1608Metric
R4: 5k RMON; R_0603_1608Metric
R5: OV top; R_0603_1608Metric
R6: OV bot; R_0603_1608Metric
R7: UV top; R_0603_1608Metric
R8: UV bot; R_0603_1608Metric
R9: RBOOT; R_0603_1608Metric
R10, R17, R23: FB top; R_0603_1608Metric
R11, R18, R24: FB bot; R_0603_1608Metric
R12: RT; R_0603_1608Metric
R13: EN top; R_0603_1608Metric
R14: EN bot; R_0603_1608Metric
R15, R38: 100k FLT pu; R_0603_1608Metric
R16: 100k PG pu; R_0603_1608Metric
R19, R20: 60R term; R_0603_1608Metric
R21: 10k STB pd; R_0603_1608Metric
R22: 10k REFCLK; R_0603_1608Metric
R25, R26, R27, R28: 2k2 pullup; R_0603_1608Metric
R29: 100k RST; R_0603_1608Metric
R30: 2k2 mic bias; R_0603_1608Metric
R31, R32: 10k bias; R_0603_1608Metric
R33, R34, R35, R36: 10k tie-off; R_0603_1608Metric
R37: 36k ILIM; R_0603_1608Metric
R39: 10k Rp CC1; R_0603_1608Metric
R40: 10k Rp CC2; R_0603_1608Metric
R41: 0R ID; R_0603_1608Metric
R42: 100k Vsense; R_0603_1608Metric
R43: 56k Vsense; R_0603_1608Metric
R44, R45, R46, R47: 10k pullup; R_0603_1608Metric
R48: 10k JTAG Vref; R_0603_1608Metric
R49: 47k min; R_0603_1608Metric
U1: LM74930-Q1; Texas_RGE0024H_VQFN-24-1EP_4x4mm_P0.5mm_EP2.7x2.7mm
U2: LM61460-Q1; TI_RJR0014A_VQFN-HR-14_4x3.5mm
U3: TLV767-Q1; Texas_DRB0008A
U4: TCAN1044V-Q1; SOIC-8_3.9x4.9mm_P1.27mm
U5: SN65DSI85-Q1; Texas_TQFP-64-1EP_10x10mm_P0.5mm_EP8x8mm_Mask4.44x4.44mm
U6: TLV767-Q1 3V3; Texas_DRB0008A
U7, U8: SN74AXC4T245-Q1; TSSOP-16_4.4x5mm_P0.65mm
U9: PCM3168A-Q1; Texas_TQFP-64-1EP_10x10mm_P0.5mm_EP8x8mm_Mask4.44x4.44mm
U10: TPS2557-Q1; Texas_DRB0008A

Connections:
+1V8: C10.1, C12.1, C15.1, C16.1, C17.1, C18.1, C19.1, C20.1, C21.1, C24.1, C26.1, Q3.1 (G), Q4.1 (G), R17.1, R25.2, R26.2, R38.2, R44.2, R45.2, R46.2, R47.2, R48.2, U3.1 (OUT), U4.5 (VIO), U5.3 (VCC1), U5.14 (VCC2), U5.18 (VCC3), U5.32 (VCC4), U5.35 (VCC5), U5.40 (VCC6), U5.43 (VCC7), U5.48 (VCC8), U5.49 (VCC9), U5.55 (VCC10), U5.58 (VCC11), U5.63 (VCC12), U7.1 (VCCA), U7.2 (1DIR), U7.3 (2DIR), U8.1 (VCCA), U8.3 (2DIR)
+3V3: C23.1, C25.1, C27.1, C33.1, C34.1, R23.1, R27.2, R28.2, R29.1, U6.1 (OUT), U7.16 (VCCB), U8.16 (VCCB), U9.12 (VDD2), U9.46 (VDD1)
+5V: C8.1, C9.1, C11.1, C22.1, C31.1, C32.1, C37.1, J1.251 (VCC), J1.253 (VCC), J1.255 (VCC), J1.257 (VCC), J1.259 (VCC), L1.2, R10.1, R15.2, R16.2, R30.1, R39.2, R40.2, U2.1 (BIAS), U3.8 (IN), U4.3 (VCC), U6.8 (IN), U9.3 (VCCAD2), U9.14 (VCCDA1), U9.34 (VCCDA2), U9.49 (VCCAD1), U10.2 (IN1), U10.3 (IN2)
+12V_PROT: C5.1, Q1.2 (D), R13.1, U1.18 (ISCP), U1.24 (C), U2.8 (VIN1), U2.12 (VIN2)
AOUT_FL_N: J5.2 (FL_N), U9.32 (VOUT1N)
AOUT_FL_P: J5.1 (FL_P), U9.31 (VOUT1P)
AOUT_FR_N: J5.4 (FR_N), U9.30 (VOUT2N)
AOUT_FR_P: J5.3 (FR_P), U9.29 (VOUT2P)
AOUT_RL_N: J5.6 (RL_N), U9.28 (VOUT3N)
AOUT_RL_P: J5.5 (RL_P), U9.27 (VOUT3P)
AOUT_RR_N: J5.8 (RR_N), U9.26 (VOUT4N)
AOUT_RR_P: J5.7 (RR_P), U9.25 (VOUT4P)
AOUT_SUB_N: J5.10 (SUB_N), U9.24 (VOUT5N)
AOUT_SUB_P: J5.9 (SUB_P), U9.23 (VOUT5P)
BOOT_C: C7.1, R9.2, U2.14 (CBOOT)
BOOT_R: R9.1, U2.13 (RBOOT)
CAN1_H: J3.1 (CANH), R19.1, U4.7 (CANH)
CAN1_L: J3.2 (CANL), R20.2, U4.6 (CANL)
CAN1_RXD: J1.22 (CAN_1_RX), U4.4 (RXD)
CAN1_SPLIT: C13.1, R19.2, R20.1
CAN1_STB: R21.1, U4.8 (STB)
CAN1_TXD: J1.20 (CAN_1_TX), U4.1 (TXD)
CAP_CP: C3.1, U1.23 (CAP)
CODEC_DOUT_1V8: J1.36 (I2S_1_D_IN), U8.4 (1A1)
CODEC_DOUT_3V3: U8.13 (1B1), U9.8 (DOUT1)
CODEC_RST: C35.1, R29.2, U9.4 (RST)
CODEC_SCL_3V3: Q4.2 (D), R28.1, U9.42 (SCL)
CODEC_SDA_3V3: Q3.2 (D), R27.1, U9.43 (SDA)
COMMON: Q1.3 (S), Q2.3 (S), U1.2 (A), U1.15 (OUT)
CS_PLUS: R2.2, U1.20 (CS+)
DGATE: Q1.1 (G), U1.1 (DGATE)
DSI_BRIDGE_EN: J1.17 (GPIO_9_DSI), U5.2 (EN)
DSI_CLK_N: J1.35 (DSI_1_CLK_N), U5.25 (DACN)
DSI_CLK_P: J1.37 (DSI_1_CLK_P), U5.24 (DACP)
DSI_D0_N: J1.47 (DSI_1_D0_N), U5.20 (DA0N)
DSI_D0_P: J1.49 (DSI_1_D0_P), U5.19 (DA0P)
DSI_D1_N: J1.41 (DSI_1_D1_N), U5.22 (DA1N)
DSI_D1_P: J1.43 (DSI_1_D1_P), U5.21 (DA1P)
DSI_D2_N: J1.29 (DSI_1_D2_N), U5.28 (DA2N)
DSI_D2_P: J1.31 (DSI_1_D2_P), U5.27 (DA2P)
DSI_D3_N: J1.23 (DSI_1_D3_N), U5.30 (DA3N)
DSI_D3_P: J1.25 (DSI_1_D3_P), U5.29 (DA3P)
DSI_I2C_SCL: J1.55 (I2C_2_DSI_SCL), U5.15 (SCL)
DSI_I2C_SDA: J1.53 (I2C_2_DSI_SDA), U5.16 (SDA)
EN_5V: R13.2, R14.1, U2.7 (EN/SYNC)
FB_1V8: R17.2, R18.1, U3.3 (FB)
FB_3V3: R23.2, R24.1, U6.3 (FB)
FB_5V: R10.2, R11.1, U2.4 (FB)
GND: C1.2, C2.2, C4.2, C5.2, C6.2, C8.2, C9.2, C10.2, C11.2, C12.2, C13.2, C14.2, C15.2, C16.2, C17.2, C18.2, C19.2, C20.2, C21.2, C22.2, C23.2, C24.2, C25.2, C26.2, C27.2, C28.2, C29.2, C30.2, C31.2, C32.2, C33.2, C34.2, C35.2, C37.2, C38.2, C39.2, D1.2, D2.2, D3.2, D4.2, J1.10 (GND), J1.11 (GND), J1.18 (GND), J1.27 (GND), J1.28 (GND), J1.33 (GND), J1.39 (GND), J1.40 (GND), J1.45 (GND), J1.50 (GND), J1.51 (GND), J1.65 (GND), J1.68 (GND), J1.71 (GND), J1.77 (GND), J1.83 (GND), J1.86 (GND), J1.89 (GND), J1.97 (GND), J1.98 (GND), J1.103 (GND), J1.109 (GND), J1.110 (GND), J1.115 (GND), J1.121 (GND), J1.122 (GND), J1.127 (GND), J1.134 (GND), J1.145 (GND), J1.146 (GND), J1.158 (GND), J1.167 (GND), J1.170 (GND), J1.173 (GND), J1.179 (GND), J1.182 (GND), J1.194 (GND), J1.195 (GND), J1.204 (GND), J1.209 (GND), J1.223 (GND), J1.224 (GND), J1.229 (GND), J1.230 (GND), J1.236 (GND), J1.242 (GND), J1.243 (GND), J2.2 (GND), J3.3 (GND), J4.21 (GND1), J4.22 (GND2), J5.11 (GND), J6.3 (GND), J7.8 (GND), J7.9 (SHIELD), J8.8 (GND), J9.4 (GND), J10.2 (GND), R3.2, R4.2, R6.2, R8.2, R11.2, R12.2, R14.2, R18.2, R21.2, R22.2, R24.2, R33.2, R34.2, R35.2, R36.2, R37.2, R41.2, R43.2, U1.13 (GND), U2.3 (AGND), U2.9 (PGND1), U2.11 (PGND2), U3.4 (GND), U3.6 (GND2), U3.9 (EP), U4.2 (GND), U5.23 (GND1), U5.26 (GND2), U5.52 (GND3), U5.64 (ADDR), U5.65 (EP), U6.4 (GND), U6.6 (GND2), U6.9 (EP), U7.8 (GND1), U7.9 (GND2), U7.14 (2OE), U7.15 (1OE), U8.2 (1DIR), U8.8 (GND1), U8.9 (GND2), U8.14 (2OE), U8.15 (1OE), U9.2 (AGNDAD2), U9.11 (DGND2), U9.16 (AGNDDA1), U9.33 (AGNDDA2), U9.45 (ADR0), U9.47 (DGND1), U9.48 (MODE), U9.50 (AGNDAD1), U9.60 (VREFAD2), U9.65 (EP), U10.1 (GND), U10.9 (EP)
HGATE: Q2.1 (G), U1.14 (HGATE)
I2C1_SCL_1V8: J1.14 (I2C_1_SCL), Q4.3 (S), R26.1
I2C1_SDA_1V8: J1.12 (I2C_1_SDA), Q3.3 (S), R25.1
I2S_BCK_1V8: J1.30 (I2S_1_BCLK), U7.4 (1A1)
I2S_BCK_3V3: U7.13 (1B1), U9.7 (BCKAD), U9.36 (BCKDA)
I2S_DIN_1V8: J1.34 (I2S_1_D_OUT), U7.6 (2A1)
I2S_DIN_3V3: U7.11 (2B1), U9.37 (DIN1)
I2S_LRCK_1V8: J1.32 (I2S_1_SYNC), U7.5 (1A2)
I2S_LRCK_3V3: U7.12 (1B2), U9.6 (LRCKAD), U9.35 (LRCKDA)
I2S_SCKI_1V8: J1.38 (I2S_1_MCLK), U7.7 (2A2)
I2S_SCKI_3V3: U7.10 (2B2), U9.41 (SCKI)
ILIM: R3.1, U1.11 (ILIM)
IMON: R4.1, U1.10 (IMON)
JTAG_TCK: J1.9 (JTAG_1_TCK), J8.3 (TCK)
JTAG_TDI: J1.1 (JTAG_1_TDI), J8.5 (TDI)
JTAG_TDO: J1.5 (JTAG_1_TDO), J8.4 (TDO)
JTAG_TMS: J1.13 (JTAG_1_TMS), J8.2 (TMS)
JTAG_TRST: J1.3 (JTAG_1_TRST#), J8.6 (TRST)
JTAG_VREF: J1.7 (JTAG_1_VREF), J8.1 (VREF), R48.1
LVDS_A_CLKN: J4.10 (A_CLKN), U5.39 (A_CLKN)
LVDS_A_CLKP: J4.9 (A_CLKP), U5.38 (A_CLKP)
LVDS_A_Y0N: J4.2 (A_Y0N), U5.47 (A_Y0N)
LVDS_A_Y0P: J4.1 (A_Y0P), U5.46 (A_Y0P)
LVDS_A_Y1N: J4.4 (A_Y1N), U5.45 (A_Y1N)
LVDS_A_Y1P: J4.3 (A_Y1P), U5.44 (A_Y1P)
LVDS_A_Y2N: J4.6 (A_Y2N), U5.42 (A_Y2N)
LVDS_A_Y2P: J4.5 (A_Y2P), U5.41 (A_Y2P)
LVDS_A_Y3N: J4.8 (A_Y3N), U5.37 (A_Y3N)
LVDS_A_Y3P: J4.7 (A_Y3P), U5.36 (A_Y3P)
LVDS_B_CLKN: J4.20 (B_CLKN), U5.54 (B_CLKN)
LVDS_B_CLKP: J4.19 (B_CLKP), U5.53 (B_CLKP)
LVDS_B_Y0N: J4.12 (B_Y0N), U5.62 (B_Y0N)
LVDS_B_Y0P: J4.11 (B_Y0P), U5.61 (B_Y0P)
LVDS_B_Y1N: J4.14 (B_Y1N), U5.60 (B_Y1N)
LVDS_B_Y1P: J4.13 (B_Y1P), U5.59 (B_Y1P)
LVDS_B_Y2N: J4.16 (B_Y2N), U5.57 (B_Y2N)
LVDS_B_Y2P: J4.15 (B_Y2P), U5.56 (B_Y2P)
LVDS_B_Y3N: J4.18 (B_Y3N), U5.51 (B_Y3N)
LVDS_B_Y3P: J4.17 (B_Y3P), U5.50 (B_Y3P)
MIC_BIAS_P: C36.1, J6.1 (MIC_P), R30.2
MIC_IN_N: J6.2 (MIC_N), R32.2, U9.51 (VIN1N)
MIC_IN_P: C36.2, R31.2, U9.52 (VIN1P)
OV_DIV: R5.2, R6.1, U1.5 (OV), U1.16 (OVCLAMP)
PG_5V: R16.1, U2.5 (PGOOD)
PWR_BTN: J1.248 (CTRL_PWR_BTN_MICO#), J9.1 (PWR_BTN), R44.1
PWR_EN_MOCI: J1.254 (CTRL_PWR_EN_MOCI), U3.5 (EN), U6.5 (EN)
PWR_FLT: R15.1, U1.12 (FLT)
RECOVERY: J1.246 (CTRL_RECOVERY_MICO#), J9.2 (RECOVERY), R45.1
REFCLK_GND: R22.1, U5.17 (REFCLK)
RESET_MICO: J1.260 (CTRL_RESET_MICO#), J8.7 (RESET), J9.3 (RESET), R46.1
RESET_MOCI: J1.258 (CTRL_RESET_MOCI#), R47.1
RT_5V: R12.1, U2.6 (RT)
SENSE_OUT: Q2.2 (D), R1.2, U1.19 (CS-)
SW_5V: C7.2, L1.1, U2.10 (SW)
SW_SENSE: R5.1, R7.1, U1.3 (SW)
TMR: C4.1, U1.9 (TMR)
U8_1B2_TIE: R33.1, U8.12 (1B2)
U8_2A1_TIE: R34.1, U8.6 (2A1)
U8_2A2_TIE: R35.1, U8.7 (2A2)
U9_ADR1_TIE: R36.1, U9.44 (ADR1)
USB1_DN: D3.1, J1.163 (USB_1_D_N), J7.3 (DN)
USB1_DP: D2.1, J1.165 (USB_1_D_P), J7.2 (DP)
USB1_EN: J1.155 (USB_1_EN), U10.4 (EN)
USB1_ID: J1.161 (USB_1_ID), R41.1
USB1_OC: J1.157 (USB_1_OC#), R38.1, U10.8 (FAULT)
USB1_VBUS_SENSE: J1.159 (USB_1_VBUS), R42.2, R43.1
USB_CC1: J7.4 (CC1), R39.1
USB_CC2: J7.5 (CC2), R40.1
USB_ILIM: R37.1, U10.5 (ILIM)
USB_VBUS: C38.1, D4.1, J7.1 (VBUS), R42.1, U10.6 (OUT1), U10.7 (OUT2)
UVLO_DIV: R7.2, R8.1, U1.4 (UVLO)
VBACKUP: C39.1, J1.249 (VCC_BACKUP), R49.2
VBACKUP_CELL: J10.1 (VBAT), R49.1
VBAT_F: C1.1, C2.1, C3.2, D1.1, F1.2, R1.1, R2.1, U1.6 (EN), U1.7 (MODE), U1.22 (VS)
VBAT_IN: F1.1, J2.1 (VBAT)
VCC_LDO: C6.1, U2.2 (VCC)
VCOMAD: C28.1, R31.1, R32.1, U9.1 (VCOMAD)
VCOMDA: C29.1, U9.15 (VCOMDA)
VCORE_1V1: C14.1, U5.31 (VCORE)
VREFAD1: C30.1, U9.59 (VREFAD1)

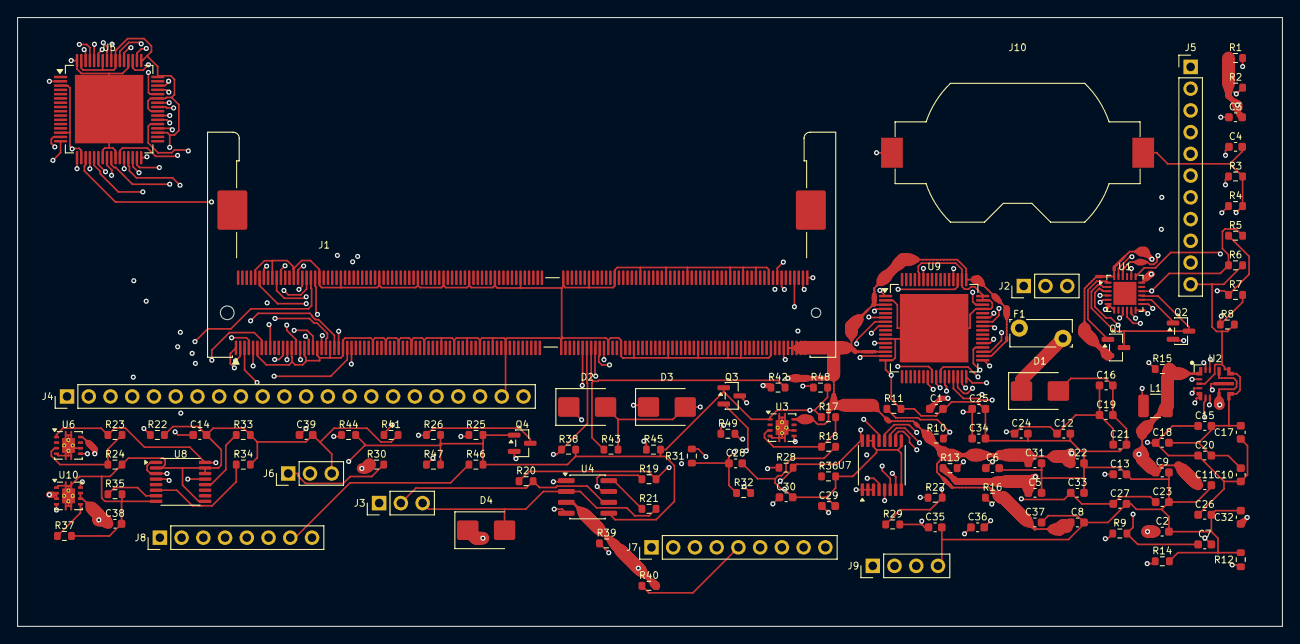
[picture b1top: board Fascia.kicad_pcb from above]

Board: 6 copper layers, 147.8 x 71.1 mm, 118 parts (0 on the bottom side), 129 nets.
